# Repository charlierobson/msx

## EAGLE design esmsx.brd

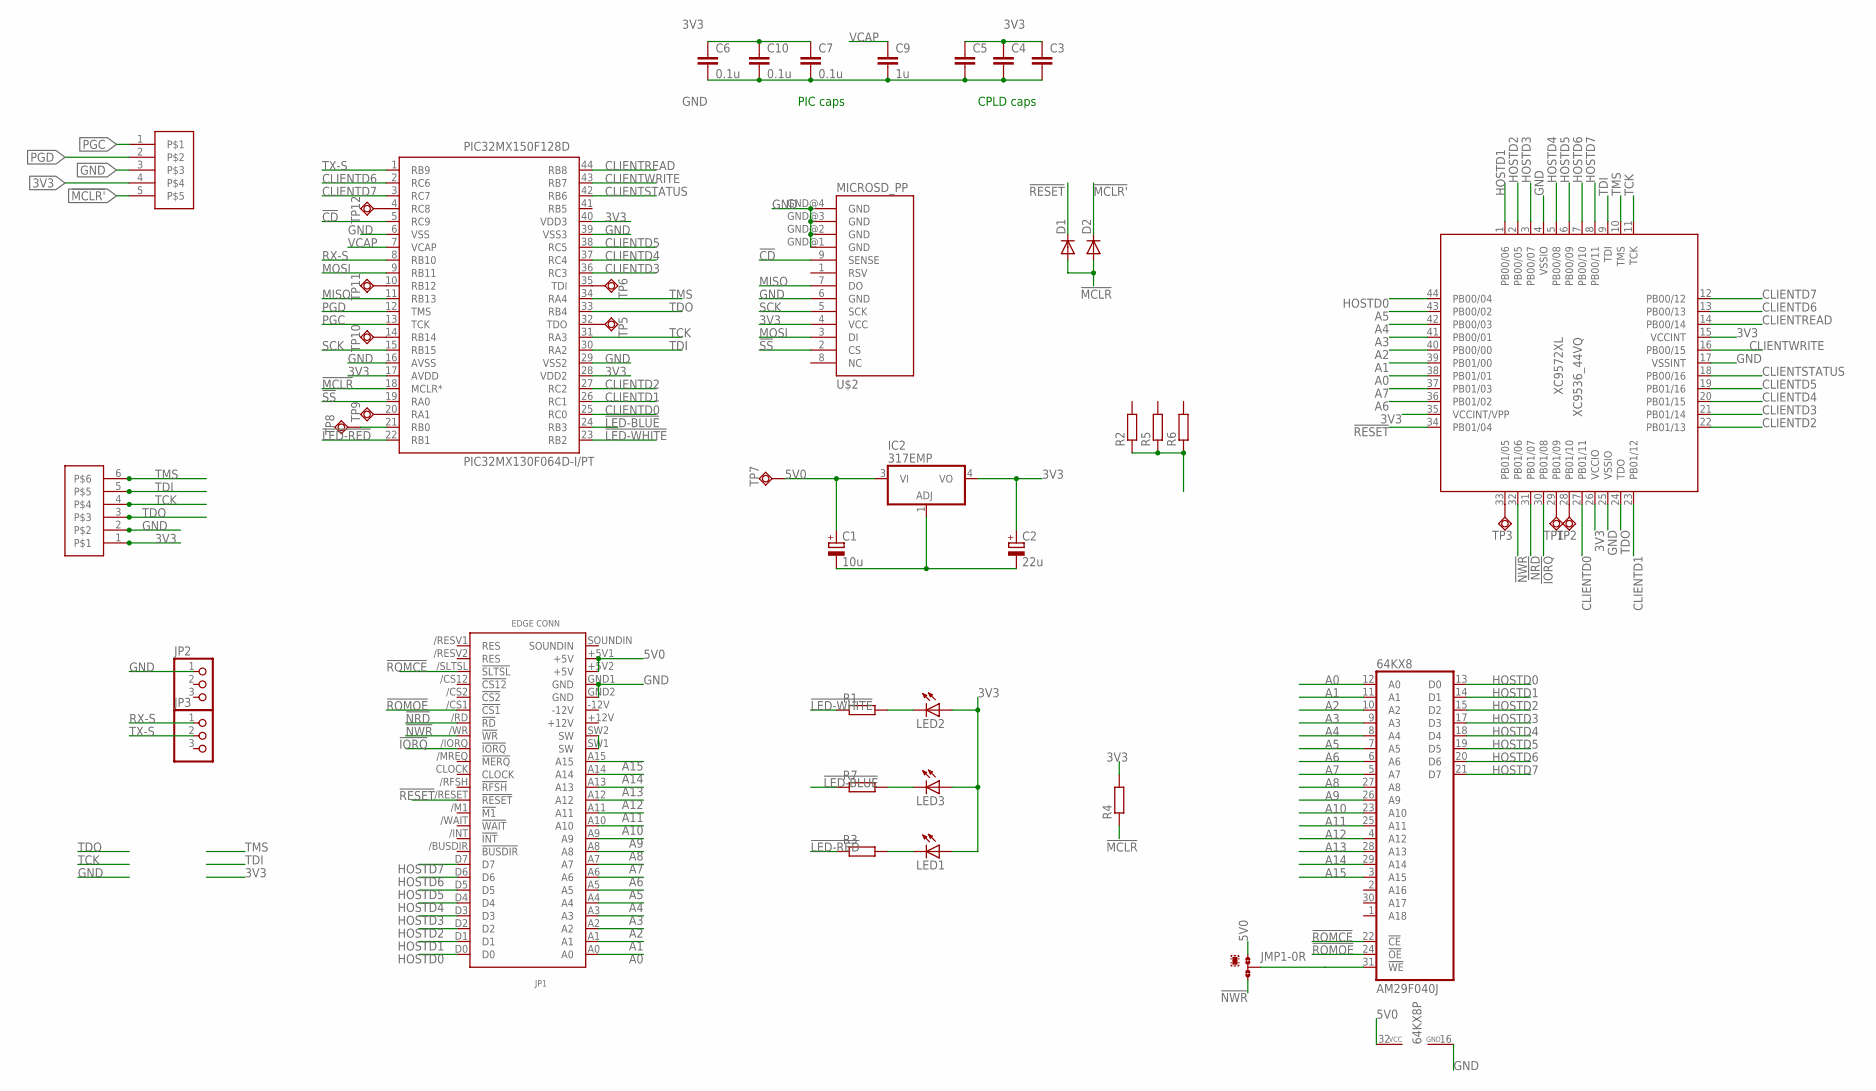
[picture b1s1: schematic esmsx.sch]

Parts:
64KX8: AM29F040J; PLCC32R
C1: 10u; SMC_B
C2: 22u; SMC_B
C3, C4, C5: C-EUC0805; C0805
C6, C7, C10: 0.1u; C0805
C9: 1u; C0805
D1, D2: DIODE-SOD123; SOD123
IC2: 317EMP; SOT223
JMP1: 0R-JUMPA; A0R-JMP
JP1: MSXCART
JP2, JP3: PINHD-1X3; 1X03
LED1, LED2, LED3: LEDCHIPLED_1206; CHIPLED_1206
PIC32MX150F128D: PIC32MX130F064D-I/PT; QFP80P1200X1200X120-44N
R1, R2, R3, R4, R5, R6, R7: R-EU_R0805W; R0805W
TP1, TP2, TP3, TP5, TP6, TP7, TP8, TP9, TP10, TP11, TP12: TPSQTP20SQ; TP20SQ
U$2: MICROSD_PP
U$3: 6PIN; 1X04-1.27MM
U$4: 5PIN; 1X05-1.27MM
XC9572XL: XC9536_44VQ; SQFP-S-10X10-44

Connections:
3V3: C2.+, C3.1, C4.1, C5.1, C6.1, C7.1, C10.1, IC2.4 (VO), LED1.A, LED2.A, LED3.A, PIC32MX150F128D.17 (AVDD), PIC32MX150F128D.28 (VDD2), PIC32MX150F128D.40 (VDD3), R4.2, U$2.4 (VCC), U$3.1, U$4.4, XC9572XL.15 (VCCINT), XC9572XL.26 (VCCIO), XC9572XL.35 (VCCINT/VPP)
5V0: 64KX8.31 (!WE), 64KX8.32 (VCC), C1.+, IC2.3 (VI), JMP1.1, JMP1.2, JP1.+5V1 (+5V), JP1.+5V2 (+5V), R2.1, R5.1, R6.1, TP7.TP
!CD: PIC32MX150F128D.5 (RC9), U$2.9 (SENSE)
!ERR': LED2.C, R1.2
!IORQ: JP1./IORQ (!IORQ), XC9572XL.30 (PB01/08)
!LED-BLUE: PIC32MX150F128D.24 (RB3), R7.1
!LED-RED: PIC32MX150F128D.22 (RB1), R3.1
!LED-WHITE: PIC32MX150F128D.23 (RB2), R1.1
!MCLR: D1.A, D2.A, PIC32MX150F128D.18 (MCLR*), R4.1
!MCLR': D2.C, U$4.5
!NRD: JP1./RD (!RD), XC9572XL.31 (PB01/07)
!NWR: JMP1.3, JP1./WR (!WR), XC9572XL.32 (PB01/06)
!RESET: D1.C, JP1./RESET (!RESET), XC9572XL.34 (PB01/04)
!ROMCE: 64KX8.22 (!CE), JP1./SLTSL (!SLTSL)
!ROMOE: 64KX8.24 (!OE), JP1./CS1 (!CS1)
!SS: PIC32MX150F128D.19 (RA0), U$2.2 (CS)
A0: 64KX8.12 (A0), JP1.A0, XC9572XL.38 (PB01/01)
A1: 64KX8.11 (A1), JP1.A1, XC9572XL.39 (PB01/00)
A2: 64KX8.10 (A2), JP1.A2, XC9572XL.40 (PB00/00)
A3: 64KX8.9 (A3), JP1.A3, XC9572XL.41 (PB00/01)
A4: 64KX8.8 (A4), JP1.A4, XC9572XL.42 (PB00/03)
A5: 64KX8.7 (A5), JP1.A5, XC9572XL.43 (PB00/02)
A6: 64KX8.6 (A6), JP1.A6, XC9572XL.36 (PB01/02)
A7: 64KX8.5 (A7), JP1.A7, XC9572XL.37 (PB01/03)
A8: 64KX8.27 (A8), JP1.A8
A9: 64KX8.26 (A9), JP1.A9
A10: 64KX8.23 (A10), JP1.A10
A11: 64KX8.25 (A11), JP1.A11
A12: 64KX8.4 (A12), JP1.A12
A13: 64KX8.28 (A13), JP1.A13
A14: 64KX8.29 (A14), JP1.A14
A15: 64KX8.3 (A15), JP1.A15
CLIENTD0: PIC32MX150F128D.25 (RC0), XC9572XL.27 (PB01/11)
CLIENTD1: PIC32MX150F128D.26 (RC1), XC9572XL.23 (PB01/12)
CLIENTD2: PIC32MX150F128D.27 (RC2), XC9572XL.22 (PB01/13)
CLIENTD3: PIC32MX150F128D.36 (RC3), XC9572XL.21 (PB01/14)
CLIENTD4: PIC32MX150F128D.37 (RC4), XC9572XL.20 (PB01/15)
CLIENTD5: PIC32MX150F128D.38 (RC5), XC9572XL.19 (PB01/16)
CLIENTD6: PIC32MX150F128D.2 (RC6), XC9572XL.13 (PB00/13)
CLIENTD7: PIC32MX150F128D.3 (RC7), XC9572XL.12 (PB00/12)
CLIENTREAD: PIC32MX150F128D.44 (RB8), XC9572XL.14 (PB00/14)
CLIENTSTATUS: PIC32MX150F128D.42 (RB6), XC9572XL.18 (PB00/16)
CLIENTWRITE: PIC32MX150F128D.43 (RB7), XC9572XL.16 (PB00/15)
GND: 64KX8.16 (GND), C1.-, C2.-, C3.2, C4.2, C5.2, C6.2, C7.2, C9.2, C10.2, IC2.1 (ADJ), JP1.GND1 (GND), JP1.GND2 (GND), JP2.1, PIC32MX150F128D.6 (VSS), PIC32MX150F128D.16 (AVSS), PIC32MX150F128D.29 (VSS2), PIC32MX150F128D.39 (VSS3), U$2.6 (GND), U$2.GND@1 (GND), U$2.GND@2 (GND), U$2.GND@3 (GND), U$2.GND@4 (GND), U$3.2, U$4.3, XC9572XL.4 (VSSIO), XC9572XL.17 (VSSINT), XC9572XL.25 (VSSIO)
HOSTD0: 64KX8.13 (D0), JP1.D0, XC9572XL.44 (PB00/04)
HOSTD1: 64KX8.14 (D1), JP1.D1, XC9572XL.1 (PB00/06)
HOSTD2: 64KX8.15 (D2), JP1.D2, XC9572XL.2 (PB00/05)
HOSTD3: 64KX8.17 (D3), JP1.D3, XC9572XL.3 (PB00/07)
HOSTD4: 64KX8.18 (D4), JP1.D4, XC9572XL.5 (PB00/08)
HOSTD5: 64KX8.19 (D5), JP1.D5, XC9572XL.6 (PB00/09)
HOSTD6: 64KX8.20 (D6), JP1.D6, XC9572XL.7 (PB00/10)
HOSTD7: 64KX8.21 (D7), JP1.D7, XC9572XL.8 (PB00/11)
MISO: PIC32MX150F128D.11 (RB13), U$2.7 (DO)
MOSI: PIC32MX150F128D.9 (RB11), U$2.3 (DI)
unnamed: LED1.C, R3.2
unnamed: JP1.SW1 (SW), JP1.SW2 (SW)
unnamed: PIC32MX150F128D.21 (RB0), TP8.TP
unnamed: TP1.TP, XC9572XL.29 (PB01/09)
unnamed: TP2.TP, XC9572XL.28 (PB01/10)
unnamed: TP3.TP, XC9572XL.33 (PB01/05)
unnamed: PIC32MX150F128D.32 (TDO), TP5.TP
unnamed: PIC32MX150F128D.35 (TDI), TP6.TP
unnamed: LED3.C, R7.2
unnamed: PIC32MX150F128D.20 (RA1), TP9.TP
unnamed: PIC32MX150F128D.14 (RB14), TP10.TP
unnamed: PIC32MX150F128D.10 (RB12), TP11.TP
unnamed: PIC32MX150F128D.4 (RC8), TP12.TP
PGC: PIC32MX150F128D.13 (TCK), U$4.1
PGD: PIC32MX150F128D.12 (TMS), U$4.2
RX-S: JP3.1, PIC32MX150F128D.8 (RB10)
SCK: PIC32MX150F128D.15 (RB15), U$2.5 (SCK)
TCK: PIC32MX150F128D.31 (RA3), U$3.4, XC9572XL.11 (TCK)
TDI: PIC32MX150F128D.30 (RA2), U$3.5, XC9572XL.9 (TDI)
TDO: PIC32MX150F128D.33 (RB4), U$3.3, XC9572XL.24 (TDO)
TMS: PIC32MX150F128D.34 (RA4), U$3.6, XC9572XL.10 (TMS)
TX-S: JP3.2, PIC32MX150F128D.1 (RB9)
VCAP: C9.1, PIC32MX150F128D.7 (VCAP)

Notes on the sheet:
CPLD caps
PIC caps

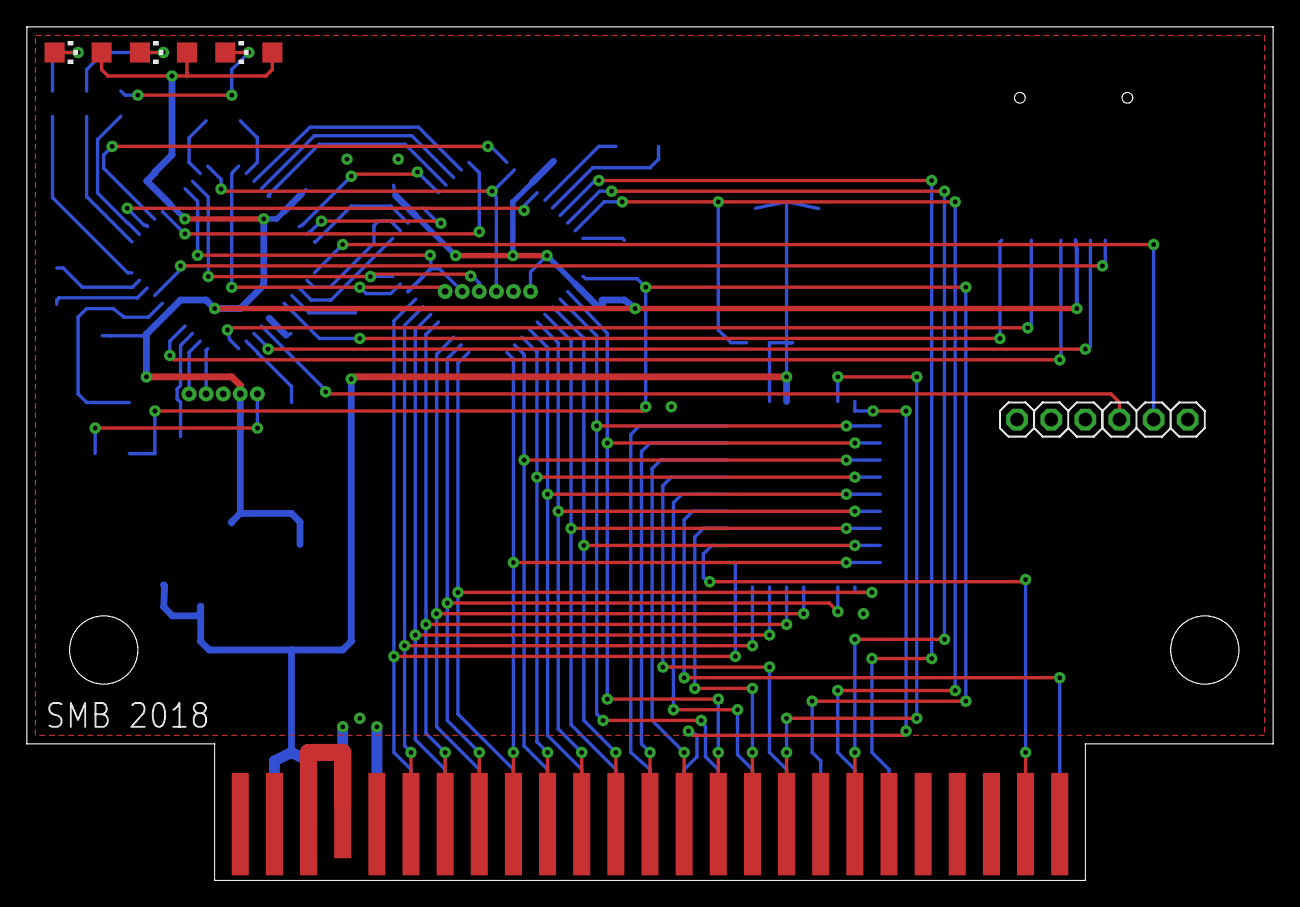
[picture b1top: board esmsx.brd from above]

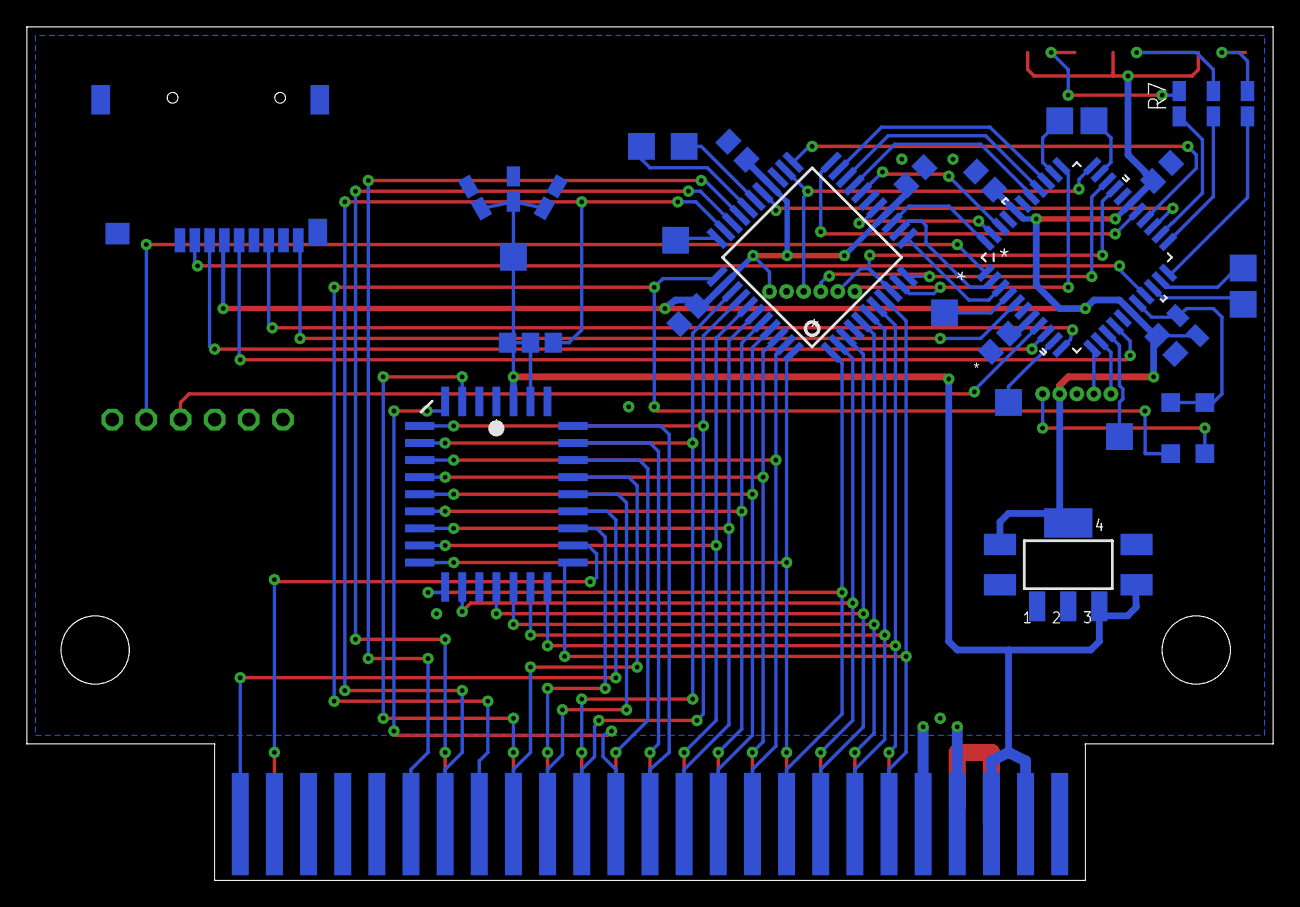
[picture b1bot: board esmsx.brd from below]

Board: 2 copper layers, 92.7 x 63.5 mm, 43 parts (35 on the bottom side), 77 nets.

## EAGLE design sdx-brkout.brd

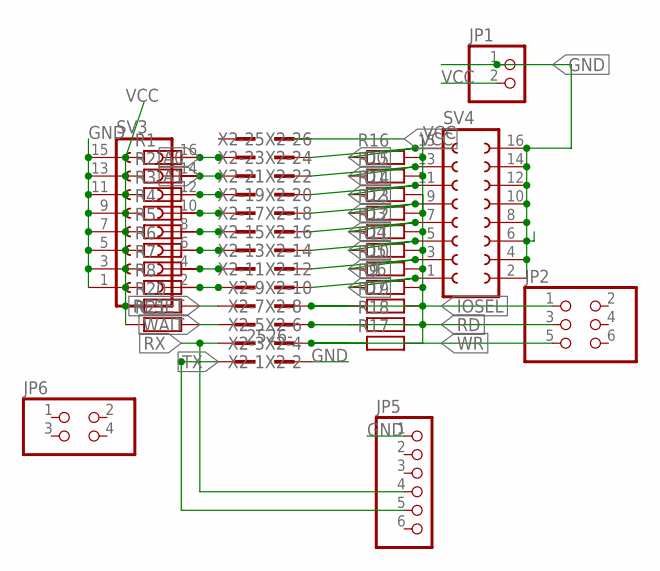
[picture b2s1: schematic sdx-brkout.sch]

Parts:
JP1: PINHD-1X2; 1X02
JP2: PINHD-2X3; 2X03
JP5: PINHD-1X6/90; 1X06/90
JP6: PINHD-2X2; 2X02
R1, R2, R3, R4, R5, R6, R7, R8, R9, R10, R11, R12, R13, R14, R15, R16, R17, R18, R19, R20, R21: R-EU_R1206W; R1206W
SV3, SV4: FE08-2
X2: 2526-; PAK100/2500-26

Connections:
!IOSEL: JP2.1, R19.1, X2.7
!RD: JP2.3, R18.1, X2.5
!RESET: R20.2, X2.8
!WAIT: R21.2, X2.6
!WR: JP2.5, R17.1, X2.3
A0: R1.2, SV3.16, X2.24
A1: R2.2, SV3.14, X2.22
D0: R16.1, SV4.15, X2.23
D1: R15.1, SV4.13, X2.21
D2: R14.1, SV4.11, X2.19
D3: R13.1, SV4.9, X2.17
D4: R12.1, SV4.7, X2.15
D5: R11.1, SV4.5, X2.13
D6: R10.1, SV4.3, X2.11
D7: R9.1, SV4.1, X2.9
GND: JP1.1, JP5.1, SV3.1, SV3.3, SV3.5, SV3.7, SV3.9, SV3.11, SV3.13, SV3.15, SV4.2, SV4.4, SV4.6, SV4.8, SV4.10, SV4.12, SV4.14, SV4.16, X2.1
unnamed: R3.2, SV3.12, X2.20
unnamed: R4.2, SV3.10, X2.18
unnamed: R5.2, SV3.8, X2.16
unnamed: R6.2, SV3.6, X2.14
unnamed: R7.2, SV3.4, X2.12
unnamed: R8.2, SV3.2, X2.10
RX: JP5.4, X2.4
TX: JP5.5, X2.2
VCC: JP1.2, R1.1, R2.1, R3.1, R4.1, R5.1, R6.1, R7.1, R8.1, R9.2, R10.2, R11.2, R12.2, R13.2, R14.2, R15.2, R16.2, R17.2, R18.2, R19.2, R20.1, R21.1

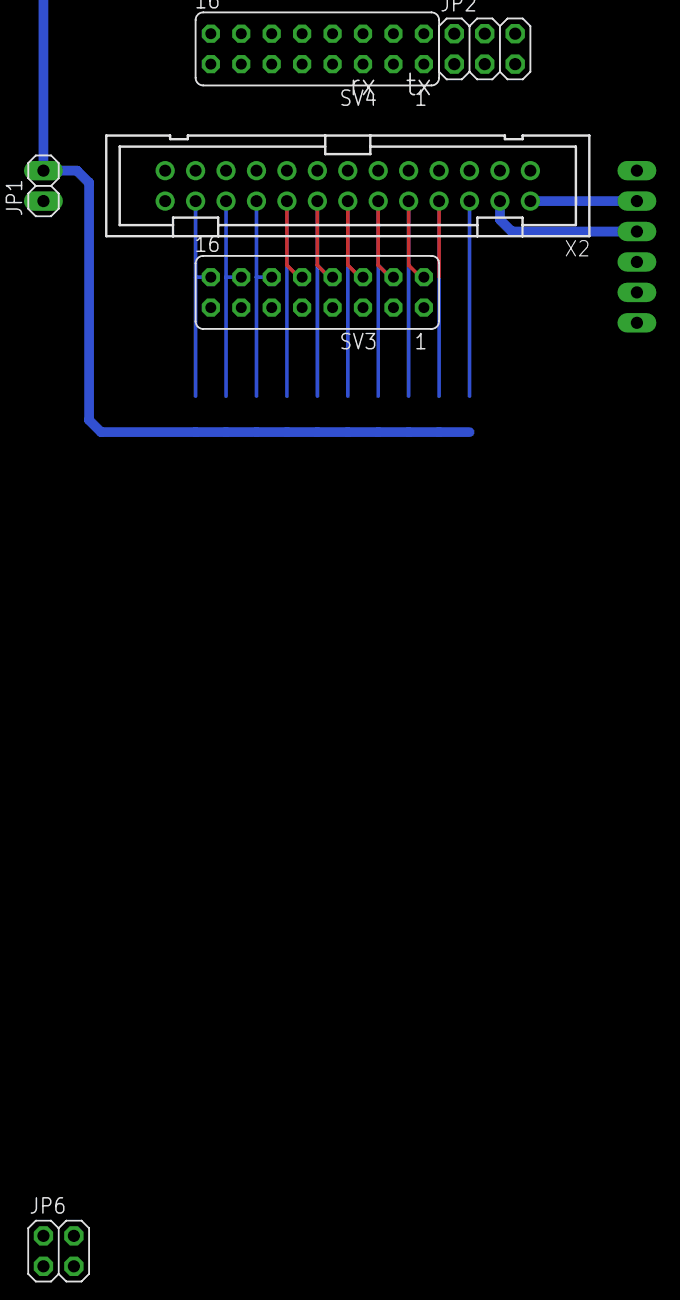
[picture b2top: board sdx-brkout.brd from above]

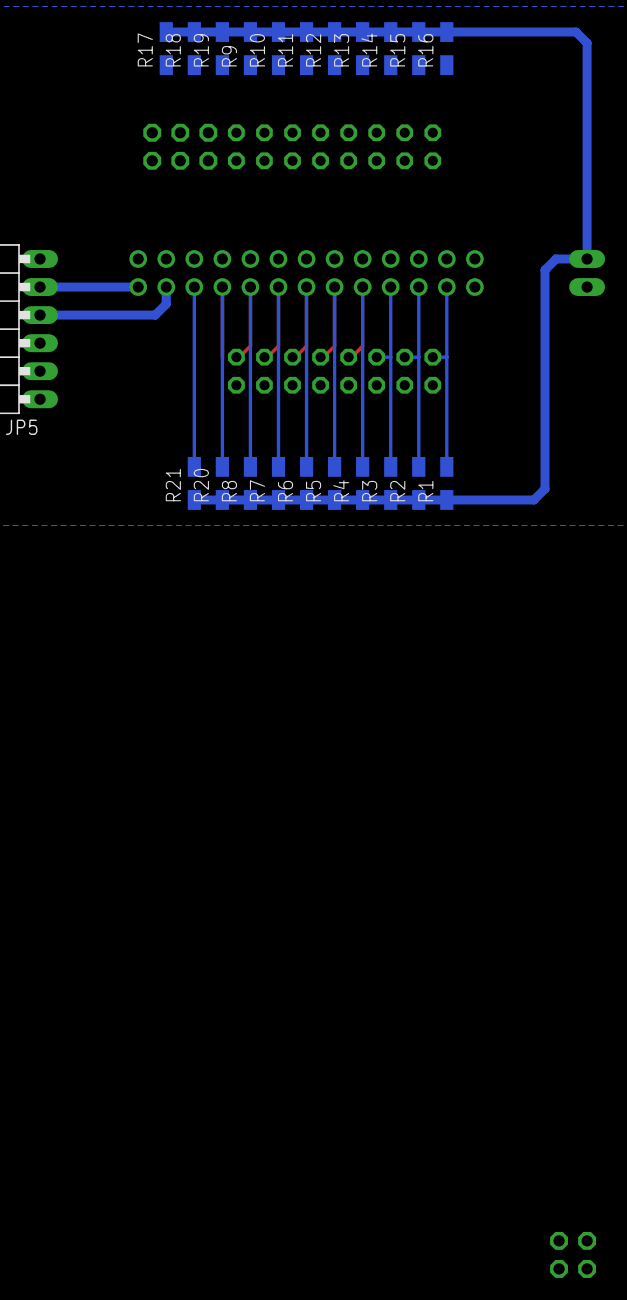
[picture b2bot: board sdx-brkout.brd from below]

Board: 2 copper layers, 28 parts (22 on the bottom side), 25 nets.

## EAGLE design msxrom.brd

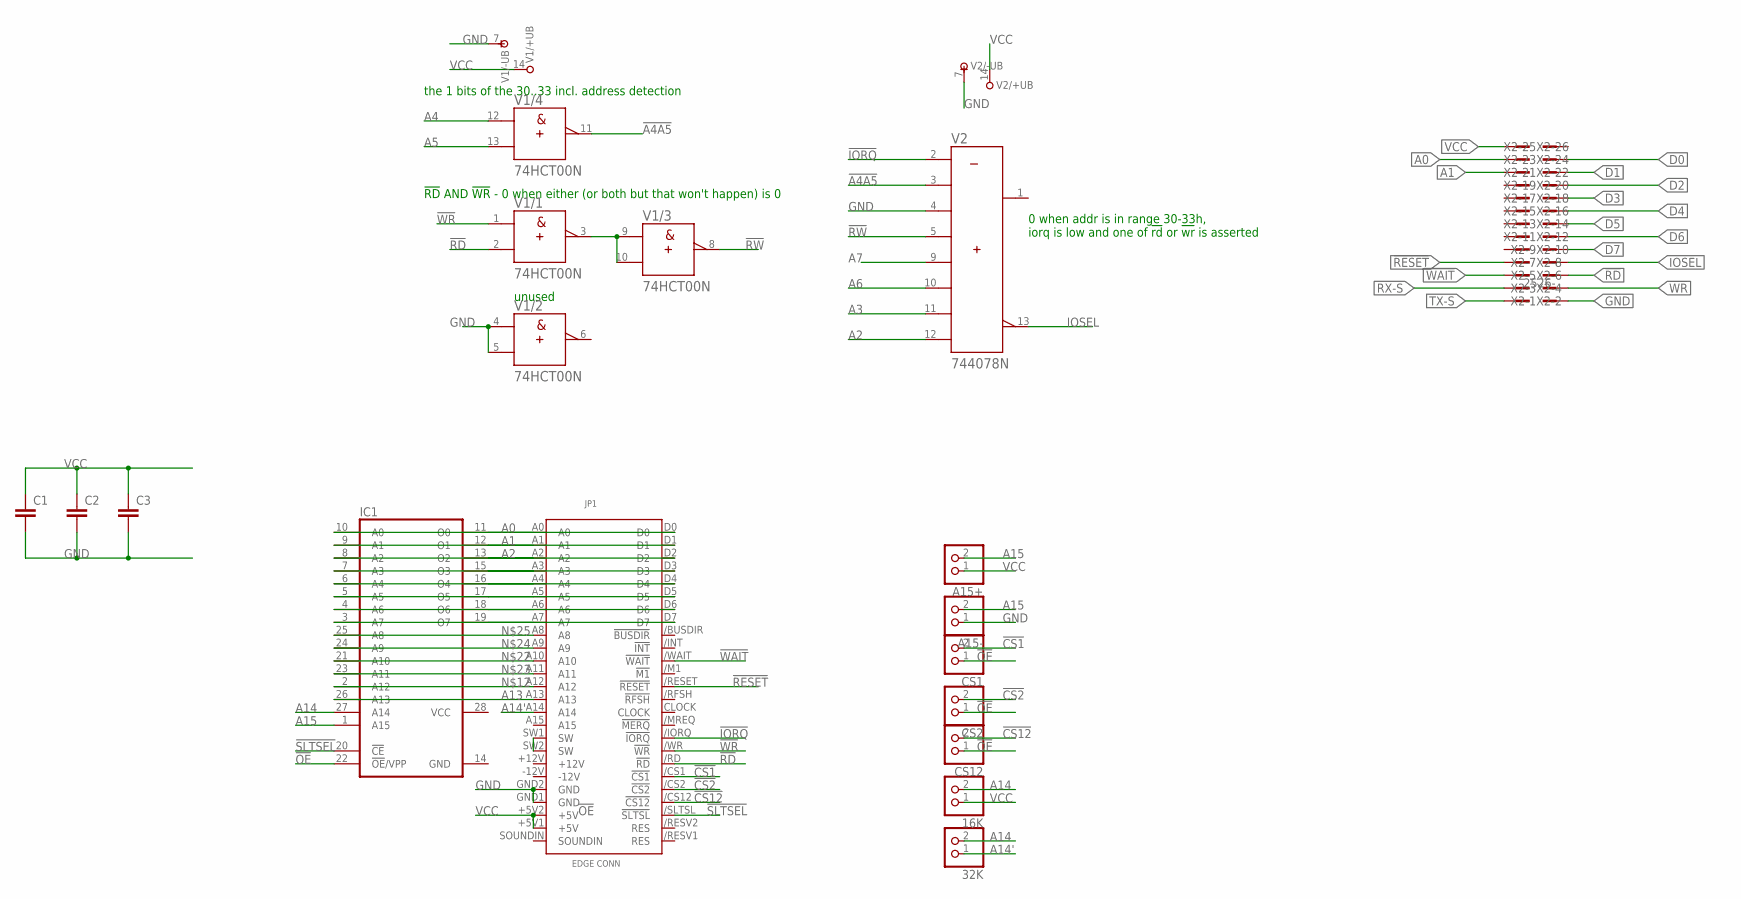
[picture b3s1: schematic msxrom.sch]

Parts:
16K, 32K: PINHD-1X2; 1X02
A15+, A15-: PINHD-1X2; 1X02
C1, C2, C3: C-EU050-025X075; C050-025X075
CS1, CS2, CS12: PINHD-1X2; 1X02
IC1: 27C512D; DIL28-6
JP1: MSXCART
V1: 74HCT00N; DIL14
V2: 744078N; DIL14
X2: 2526-; PAK100/2500-26

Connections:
!A4A5: V1.11 (Y), V2.3 (B)
!CS1: CS1.2, JP1./CS1 (!CS1)
!CS2: CS2.2, JP1./CS2 (!CS2)
!CS12: CS12.2, JP1./CS12 (!CS12)
!IORQ: JP1./IORQ (!IORQ), V2.2 (A)
!OE: CS1.1, CS2.1, CS12.1, IC1.22 (!OE!/VPP)
!RD: JP1./RD (!RD), V1.2 (B), X2.5
!RESET: JP1./RESET (!RESET), X2.8
!RW: V1.8 (Y), V2.5 (D)
!SLTSEL: IC1.20 (!CE), JP1./SLTSL (!SLTSL)
!WAIT: JP1./WAIT (!WAIT), X2.6
!WR: JP1./WR (!WR), V1.1 (A), X2.3
A0: IC1.10 (A0), JP1.A0, X2.24
A1: IC1.9 (A1), JP1.A1, X2.22
A2: IC1.8 (A2), JP1.A2, V2.12 (H)
A3: IC1.7 (A3), JP1.A3, V2.11 (G)
A4: IC1.6 (A4), JP1.A4, V1.12 (A)
A5: IC1.5 (A5), JP1.A5, V1.13 (B)
A6: IC1.4 (A6), JP1.A6, V2.10 (F)
A7: IC1.3 (A7), JP1.A7, V2.9 (E)
A13: IC1.26 (A13), JP1.A13
A14: 16K.2, 32K.2, IC1.27 (A14)
A14': 32K.1, JP1.A14
A15: A15+.2, A15-.2, IC1.1 (A15)
D0: IC1.11 (O0), JP1.D0, X2.23
D1: IC1.12 (O1), JP1.D1, X2.21
D2: IC1.13 (O2), JP1.D2, X2.19
D3: IC1.15 (O3), JP1.D3, X2.17
D4: IC1.16 (O4), JP1.D4, X2.15
D5: IC1.17 (O5), JP1.D5, X2.13
D6: IC1.18 (O6), JP1.D6, X2.11
D7: IC1.19 (O7), JP1.D7, X2.9
GND: A15-.1, C1.2, C2.2, C3.2, IC1.14 (GND), JP1.GND1 (GND), JP1.GND2 (GND), V1.4 (A), V1.5 (B), V1.7 (-UB), V2.4 (C), V2.7 (-UB), X2.1
IOSEL: V2.13 (W), X2.7
unnamed: JP1.SW1 (SW), JP1.SW2 (SW)
unnamed: V1.3 (Y), V1.9 (A), V1.10 (B)
unnamed: IC1.2 (A12), JP1.A12
unnamed: IC1.21 (A10), JP1.A10
unnamed: IC1.23 (A11), JP1.A11
unnamed: IC1.24 (A9), JP1.A9
unnamed: IC1.25 (A8), JP1.A8
RX-S: X2.4
TX-S: X2.2
VCC: 16K.1, A15+.1, C1.1, C2.1, C3.1, IC1.28 (VCC), JP1.+5V1 (+5V), JP1.+5V2 (+5V), V1.14 (+UB), V2.14 (+UB), X2.26

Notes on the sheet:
the 1 bits of the 30..33 incl. address detection
!RD! AND !WR! - 0 when either (or both but that won't happen) is 0
unused
0 when addr is in range 30-33h, iorq is low and one of !rd! or !wr! is asserted

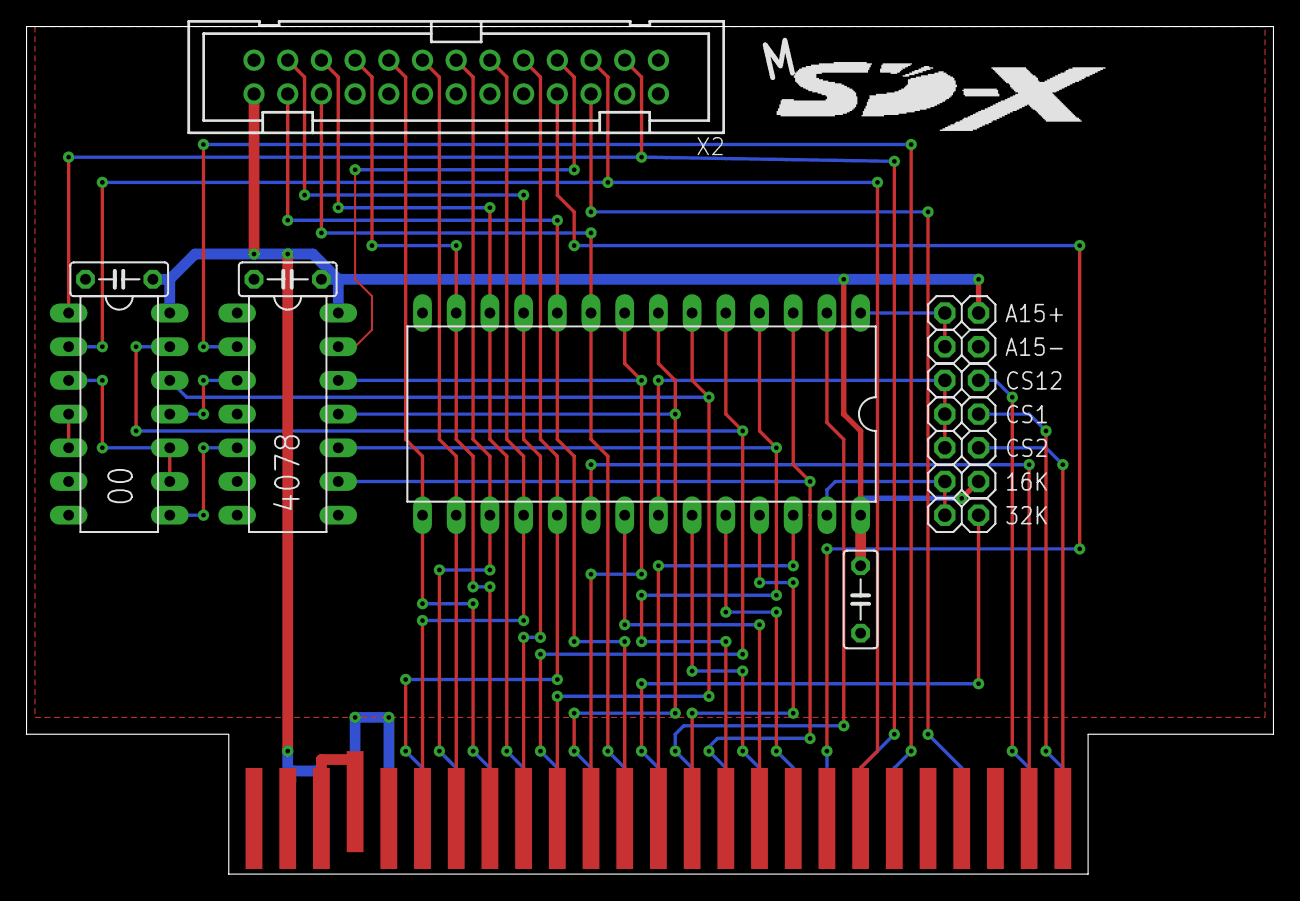
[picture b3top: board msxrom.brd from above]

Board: 2 copper layers, 94.0 x 63.9 mm, 15 parts (0 on the bottom side), 42 nets.

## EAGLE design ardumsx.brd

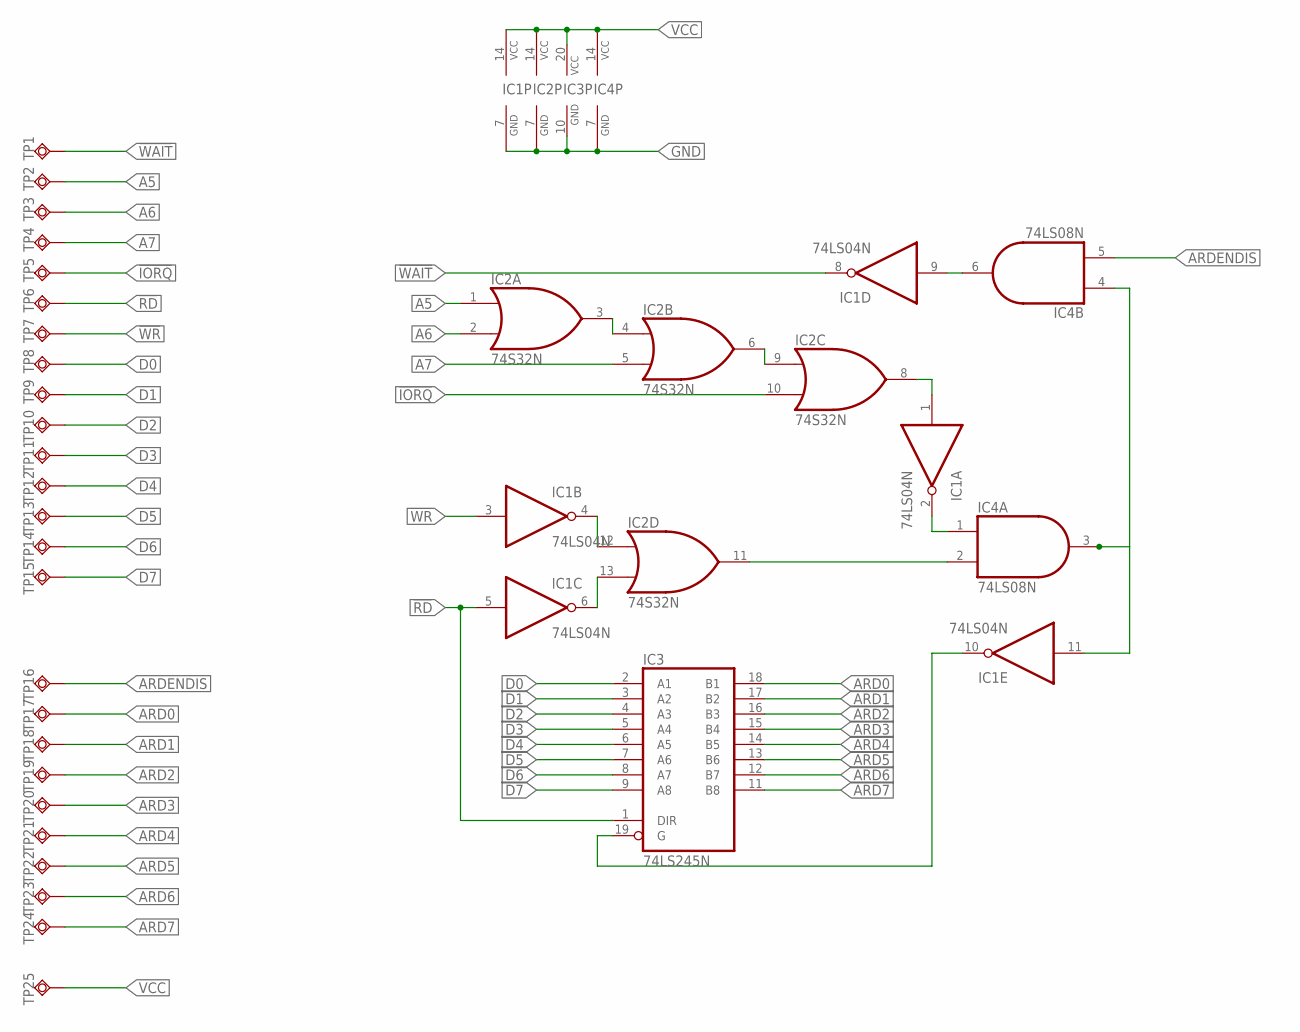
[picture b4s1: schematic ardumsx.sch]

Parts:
IC1: 74LS04N; DIL14
IC2: 74S32N; DIL14
IC3: 74LS245N; DIL20
IC4: 74LS08N; DIL14
TP1, TP2, TP3, TP4, TP5, TP6, TP7, TP8, TP9, TP10, TP11, TP12, TP13, TP14, TP15, TP16, TP17, TP18, TP19, TP20, TP21, TP22, TP23, TP24, TP25: TPSQTP17R; TP17R

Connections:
!ENABLE: IC1.10 (O), IC3.19 (G)
!IORQ: IC2.10 (I1), TP5.TP
!RD: IC1.5 (I), IC3.1 (DIR), TP6.TP
!WAIT: IC1.8 (O), TP1.TP
!WR: IC1.3 (I), TP7.TP
A5: IC2.1 (I0), TP2.TP
A6: IC2.2 (I1), TP3.TP
A7: IC2.5 (I1), TP4.TP
ARD0: IC3.18 (B1), TP17.TP
ARD1: IC3.17 (B2), TP18.TP
ARD2: IC3.16 (B3), TP19.TP
ARD3: IC3.15 (B4), TP20.TP
ARD4: IC3.14 (B5), TP21.TP
ARD5: IC3.13 (B6), TP22.TP
ARD6: IC3.12 (B7), TP23.TP
ARD7: IC3.11 (B8), TP24.TP
ARDENDIS: IC4.5 (I1), TP16.TP
D0: IC3.2 (A1), TP8.TP
D1: IC3.3 (A2), TP9.TP
D2: IC3.4 (A3), TP10.TP
D3: IC3.5 (A4), TP11.TP
D4: IC3.6 (A5), TP12.TP
D5: IC3.7 (A6), TP13.TP
D6: IC3.8 (A7), TP14.TP
D7: IC3.9 (A8), TP15.TP
GND: IC1.7 (GND), IC2.7 (GND), IC3.10 (GND), IC4.7 (GND)
unnamed: IC2.3 (O), IC2.4 (I0)
unnamed: IC2.6 (O), IC2.9 (I0)
unnamed: IC1.1 (I), IC2.8 (O)
unnamed: IC1.4 (O), IC2.12 (I0)
unnamed: IC1.6 (O), IC2.13 (I1)
unnamed: IC1.2 (O), IC4.1 (I0)
unnamed: IC2.11 (O), IC4.2 (I1)
unnamed: IC1.11 (I), IC4.3 (O), IC4.4 (I0)
unnamed: IC1.9 (I), IC4.6 (O)
VCC: IC1.14 (VCC), IC2.14 (VCC), IC3.20 (VCC), IC4.14 (VCC), TP25.TP

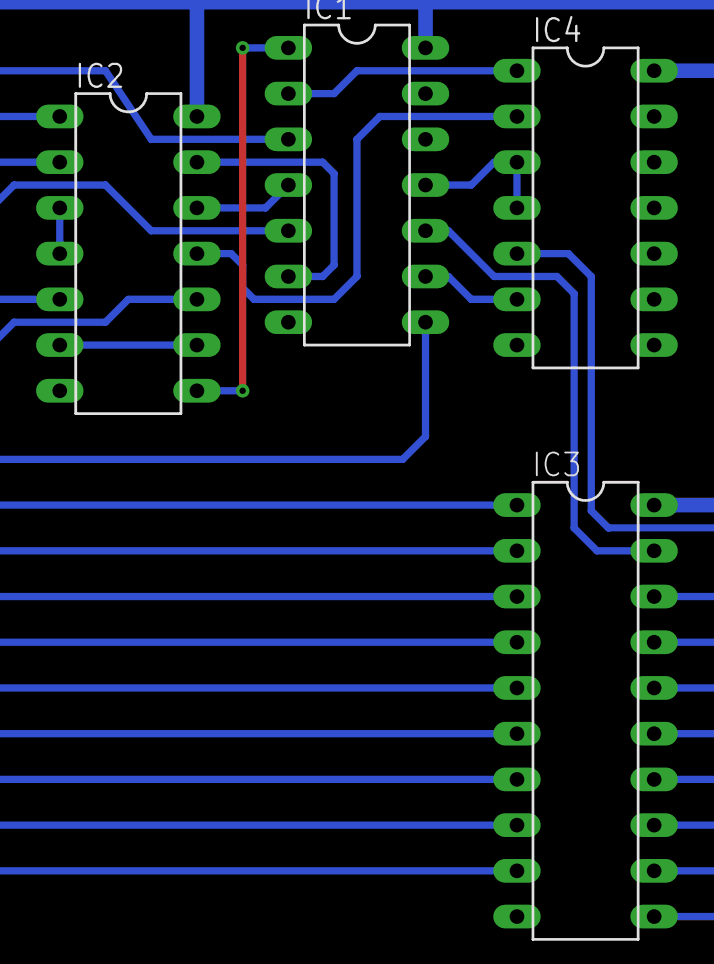
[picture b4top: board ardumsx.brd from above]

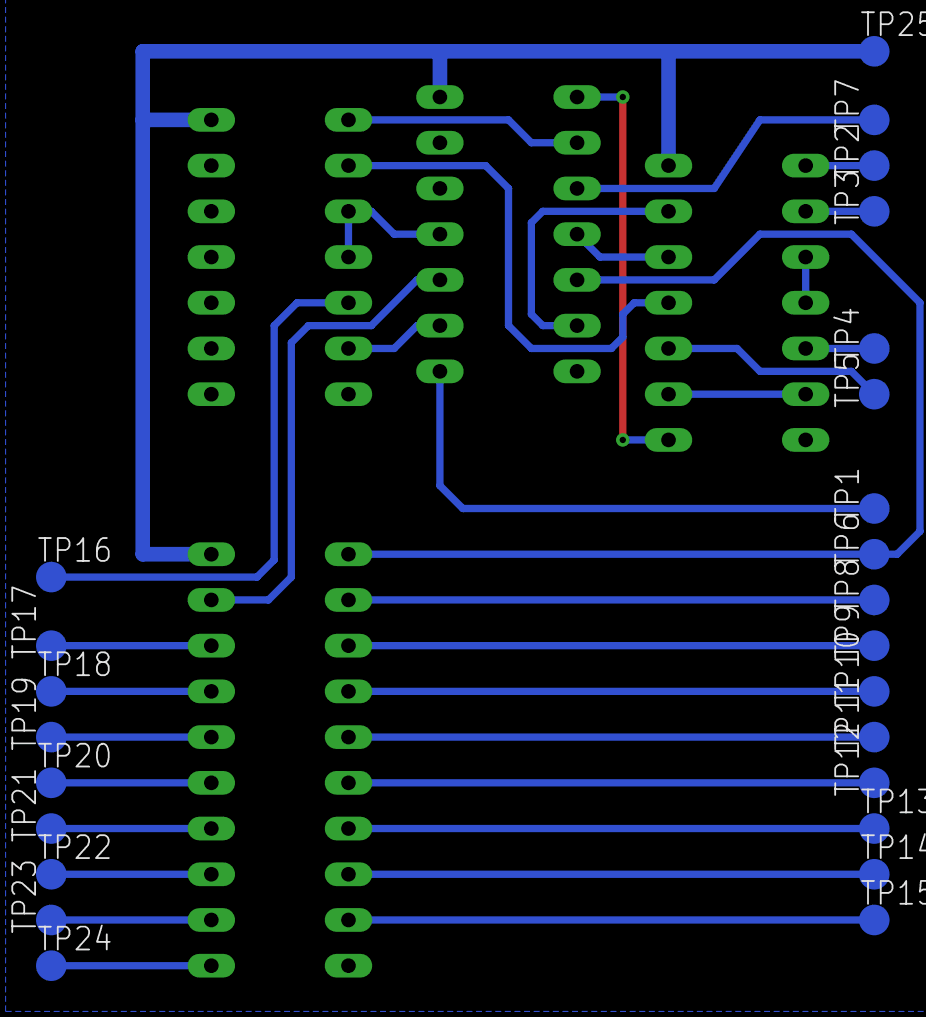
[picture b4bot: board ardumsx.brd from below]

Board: 2 copper layers, 29 parts (25 on the bottom side), 36 nets.

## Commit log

2018-06-01 with io breakout
2018-06-01 finished board but eagle broke something...
2018-06-02 with sdx connector and branding
2018-06-07 msxrom as produced
2018-06-27 adding esmsx
2018-06-27 more routing, adding a14,15
2018-06-27 more routing
2018-06-28 done but for the checking
2018-06-28 with added logo
2018-06-28 see-through logo done
2018-06-28 broken out pads and current sources for leds
2018-06-28 loose files
2018-06-30 ordered 29 06 protoype 1
2018-07-04 name parts in schematic
2018-07-04 add brd parser
2018-07-04 pins data extraction complete
2018-07-05 led section and renaming signal
2018-07-05 some initial exporting

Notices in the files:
parts and their libraries:
SparkFun: Licensing: CC v3.0 Share-Alike You are welcome to use this library for commercial purposes.
